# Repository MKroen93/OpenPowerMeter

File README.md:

# OpenPowerMeter
An open source power meter design including hardware and software

This is an open source power meter design. It is compatible with the **YHDC SCT-013-000** current clamp to measure AC mains current without contact. Optionally, 3 phase mains voltage can be measured by connecting it to the bottom screw terminal. The PCB is designed to fit into the Bopla CNC 87.5 DIN rail casing and consists on a lower and upper half of hardware which fit together through 2.54 mm pinheaders.

The lower part contains the analog frontend for converting the input signals to true rms values and for converting the input waveforms to a rectangular 3.3V output signal which can be used to detect the phase using a simple timer.

The upper part contains the MCU (ESP32) and ADC and is not yet finished.

**Please note:** This project is currently in early development and not yet tested or ready to be used.

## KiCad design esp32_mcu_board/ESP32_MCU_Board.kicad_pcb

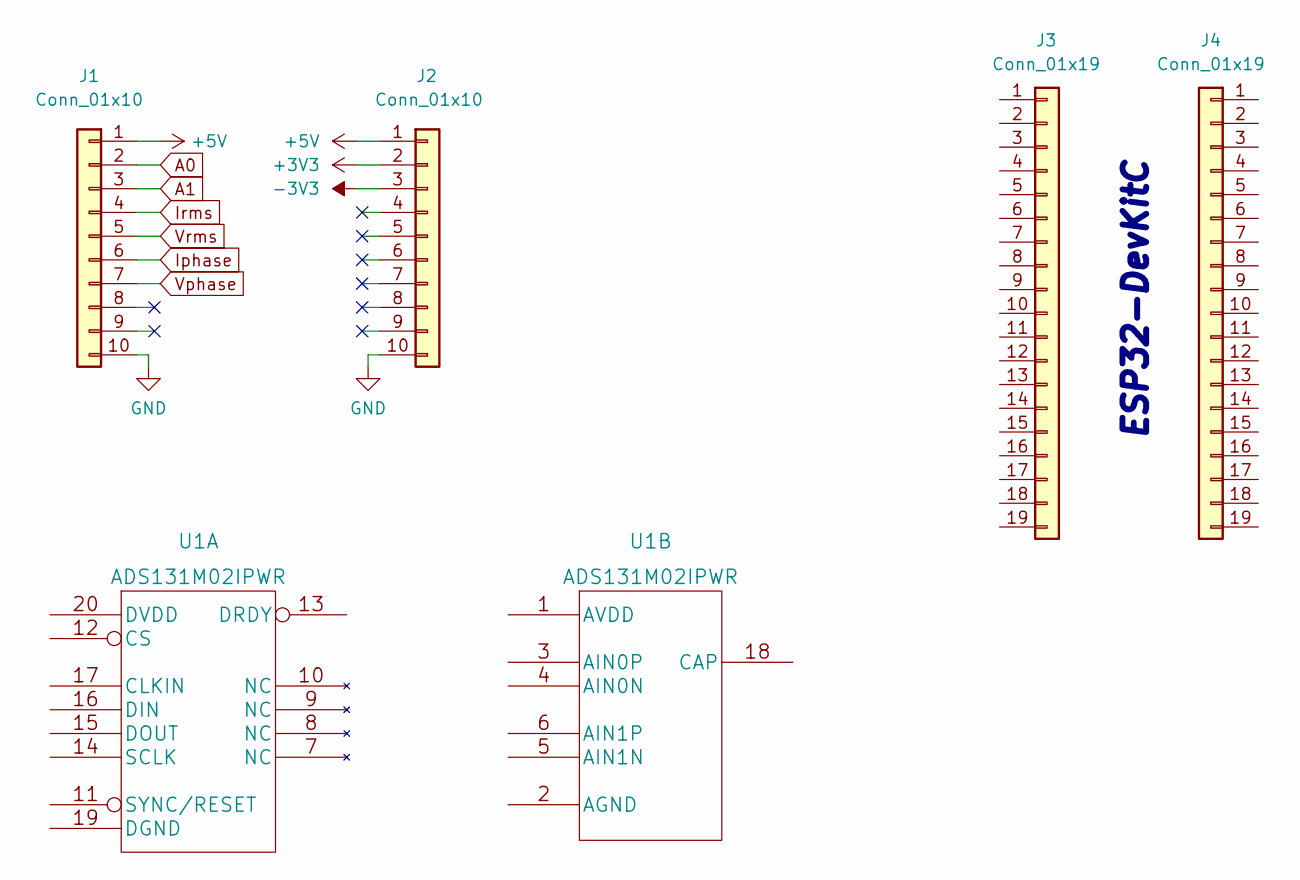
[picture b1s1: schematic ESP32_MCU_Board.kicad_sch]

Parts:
J1, J2: Conn_01x10; PinSocket_1x10_P2.54mm_Vertical
J3, J4: Conn_01x19; PinSocket_1x19_P2.54mm_Vertical
U1: ADS131M02IPWR

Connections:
+3V3: J2.2
+5V: J1.1, J2.1
-3V3: J2.3
A0: J1.2
A1: J1.3
GND: J1.10, J2.10
Iphase: J1.6
Irms: J1.4
Vphase: J1.7
Vrms: J1.5

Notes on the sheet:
ESP32-DevKitC

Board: 2 copper layers, 5 parts (2 on the bottom side), 2 nets, no tracks yet.

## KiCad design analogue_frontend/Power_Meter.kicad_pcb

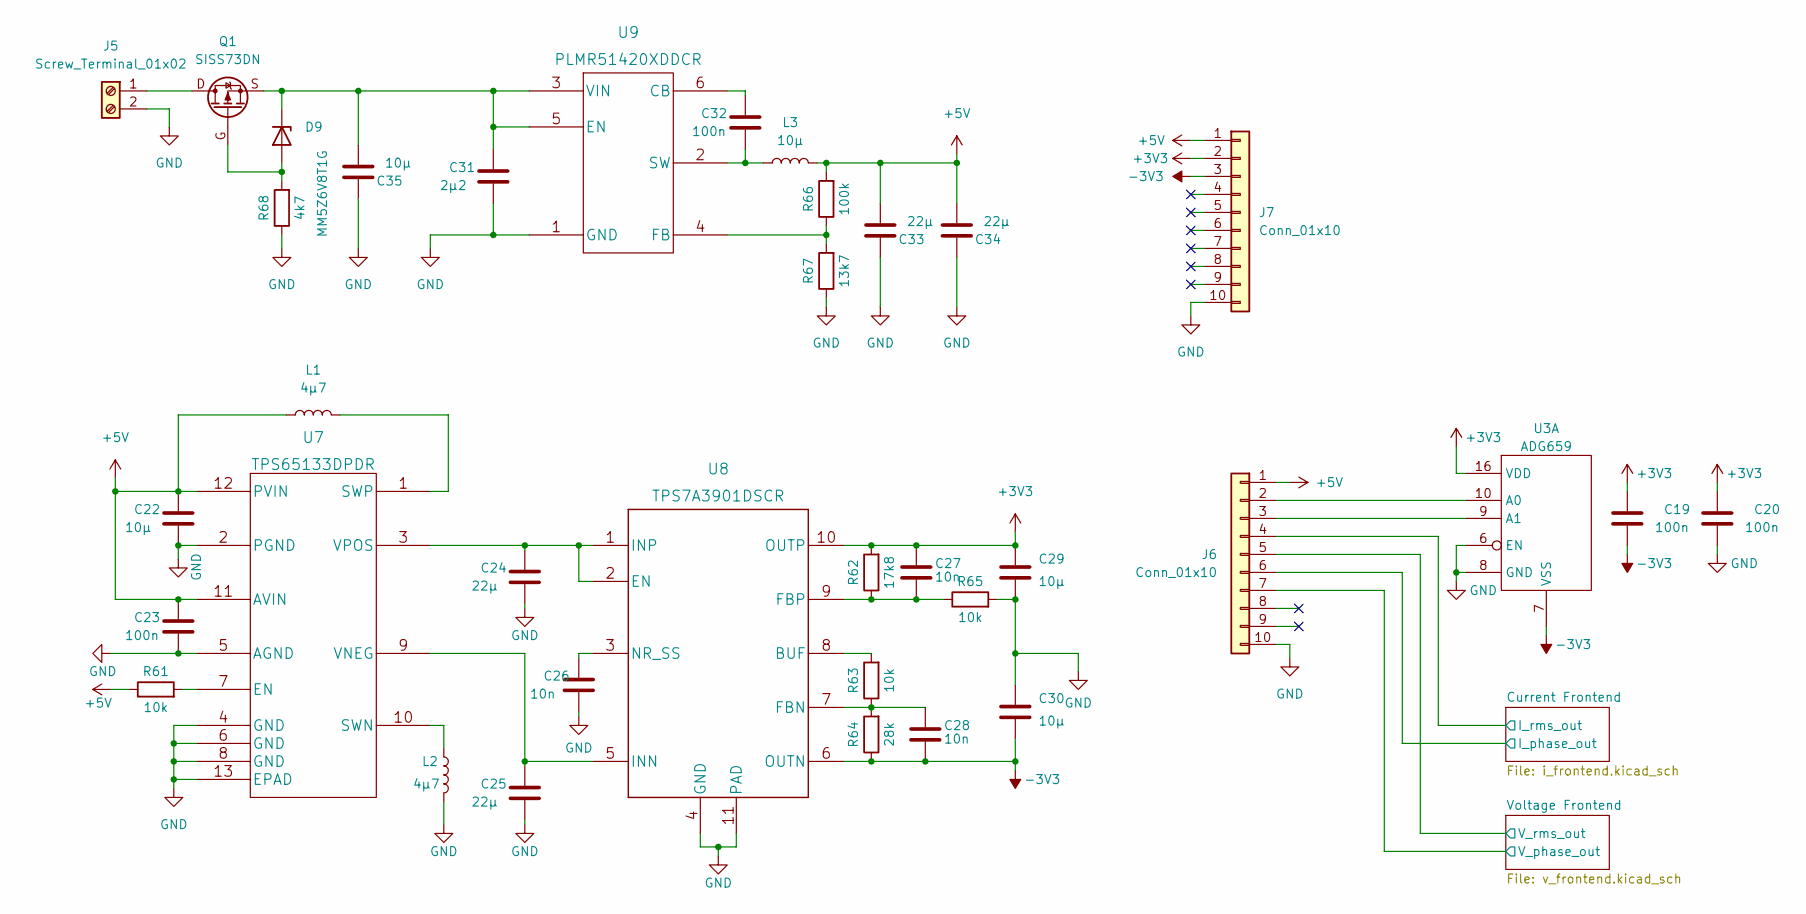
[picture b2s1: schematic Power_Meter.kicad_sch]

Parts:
C19, C23: 100n; C_0603_1608Metric_Pad1.08x0.95mm_HandSolder; Voltage rating 10V
C20: 100n; C_0603_1608Metric_Pad1.08x0.95mm_HandSolder; Voltage rating 6.3V
C22: 10µ; C_0805_2012Metric_Pad1.18x1.45mm_HandSolder; Voltage rating 10V
C24, C25, C33, C34: 22µ; C_0805_2012Metric_Pad1.18x1.45mm_HandSolder; Voltage rating 10V
C26: 10n; C_0603_1608Metric_Pad1.08x0.95mm_HandSolder; Voltage rating 10V
C27, C28: 10n; C_0603_1608Metric_Pad1.08x0.95mm_HandSolder; Voltage rating 6.3V
C29, C30: 10µ; C_0805_2012Metric_Pad1.18x1.45mm_HandSolder; Voltage rating 6.3V
C31: 2µ2; C_0805_2012Metric_Pad1.18x1.45mm_HandSolder; Voltage rating 35V
C32: 100n; C_0603_1608Metric_Pad1.08x0.95mm_HandSolder; Voltage rating 16V
C35: 10µ; C_0805_2012Metric_Pad1.18x1.45mm_HandSolder; Voltage rating 35V
D9: MM5Z6V8T1G; D_SOD-523
J5: Screw_Terminal_01x02; TerminalBlock_Phoenix_MKDS-1,5-2-5.08_1x02_P5.08mm_Horizont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
J6, J7: Conn_01x10; PinHeader_1x10_P2.54mm_Vertical
L1, L2: 4µ7; L_Coilcraft_XxL4020; Part nr. XFL4020-472ME_
L3: 10µ; L_Coilcraft_XxL4020; Part nr. XAL4040-103ME_
Q1: SISS73DN; Vishay_PowerPAK_1212-8_Single
R61, R63, R65: 10k; R_0603_1608Metric_Pad0.98x0.95mm_HandSolder
R62: 17k8; R_0603_1608Metric_Pad0.98x0.95mm_HandSolder
R64: 28k; R_0603_1608Metric_Pad0.98x0.95mm_HandSolder
R66: 100k; R_0603_1608Metric_Pad0.98x0.95mm_HandSolder
R67: 13k7; R_0603_1608Metric_Pad0.98x0.95mm_HandSolder
R68: 4k7; R_0603_1608Metric_Pad0.98x0.95mm_HandSolder
U3: ADG659; ADG659YRUZ
U7: TPS65133DPDR
U8: TPS7A3901DSCR
U9: PLMR51420XDDCR; PLMR51420XDDCT

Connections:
+3V3: C19.1, C20.1, C27.1, C29.1, J7.2, R62.2, U3.16 (VDD), U8.10 (OUTP); also elsewhere on the board
+5V: C22.1, C23.1, C33.2, C34.2, J6.1, J7.1, L1.1, L3.2, R61.1, R66.2, U7.11 (AVIN), U7.12 (PVIN)
-3V3: C19.2, C28.2, C30.2, J7.3, R64.1, U3.7 (VSS), U8.6 (OUTN); also elsewhere on the board
/Current Frontend/I_phase_out: J6.6; also elsewhere on the board
/Current Frontend/I_rms_out: J6.4; also elsewhere on the board
/Voltage Frontend/V_phase_out: J6.7; also elsewhere on the board
/Voltage Frontend/V_rms_out: J6.5; also elsewhere on the board
GND: C20.2, C22.2, C23.2, C24.2, C25.2, C26.2, C29.2, C30.1, C31.2, C33.1, C34.1, C35.1, J5.2, J6.10, J7.10, L2.2, R65.2, R67.1, R68.1, U3.6 (EN), U3.8 (GND), U7.2 (PGND), U7.4 (GND), U7.5 (AGND), U7.6 (GND), U7.8 (GND), U7.13 (EPAD), U8.4 (GND), U8.11 (PAD), U9.1 (GND); also elsewhere on the board
unnamed: C24.1, U7.3 (VPOS), U8.1 (INP), U8.2 (EN)
unnamed: C25.1, U7.9 (VNEG), U8.5 (INN)
unnamed: C26.1, U8.3 (NR_SS)
unnamed: C27.2, R62.1, R65.1, U8.9 (FBP)
unnamed: C28.1, R63.1, R64.2, U8.7 (FBN)
unnamed: C31.1, C35.2, D9.1 (K), Q1.S, U9.3 (VIN), U9.5 (EN)
unnamed: C32.1, U9.6 (CB)
unnamed: C32.2, L3.1, U9.2 (SW)
unnamed: D9.2 (A), Q1.G, R68.2
unnamed: J5.1, Q1.D
unnamed: J6.2, U3.10 (A0)
unnamed: J6.3, U3.9 (A1)
unnamed: L1.2, U7.1 (SWP)
unnamed: L2.1, U7.10 (SWN)
unnamed: R61.2, U7.7 (EN)
unnamed: R63.2, U8.8 (BUF)
unnamed: R66.1, R67.2, U9.4 (FB)

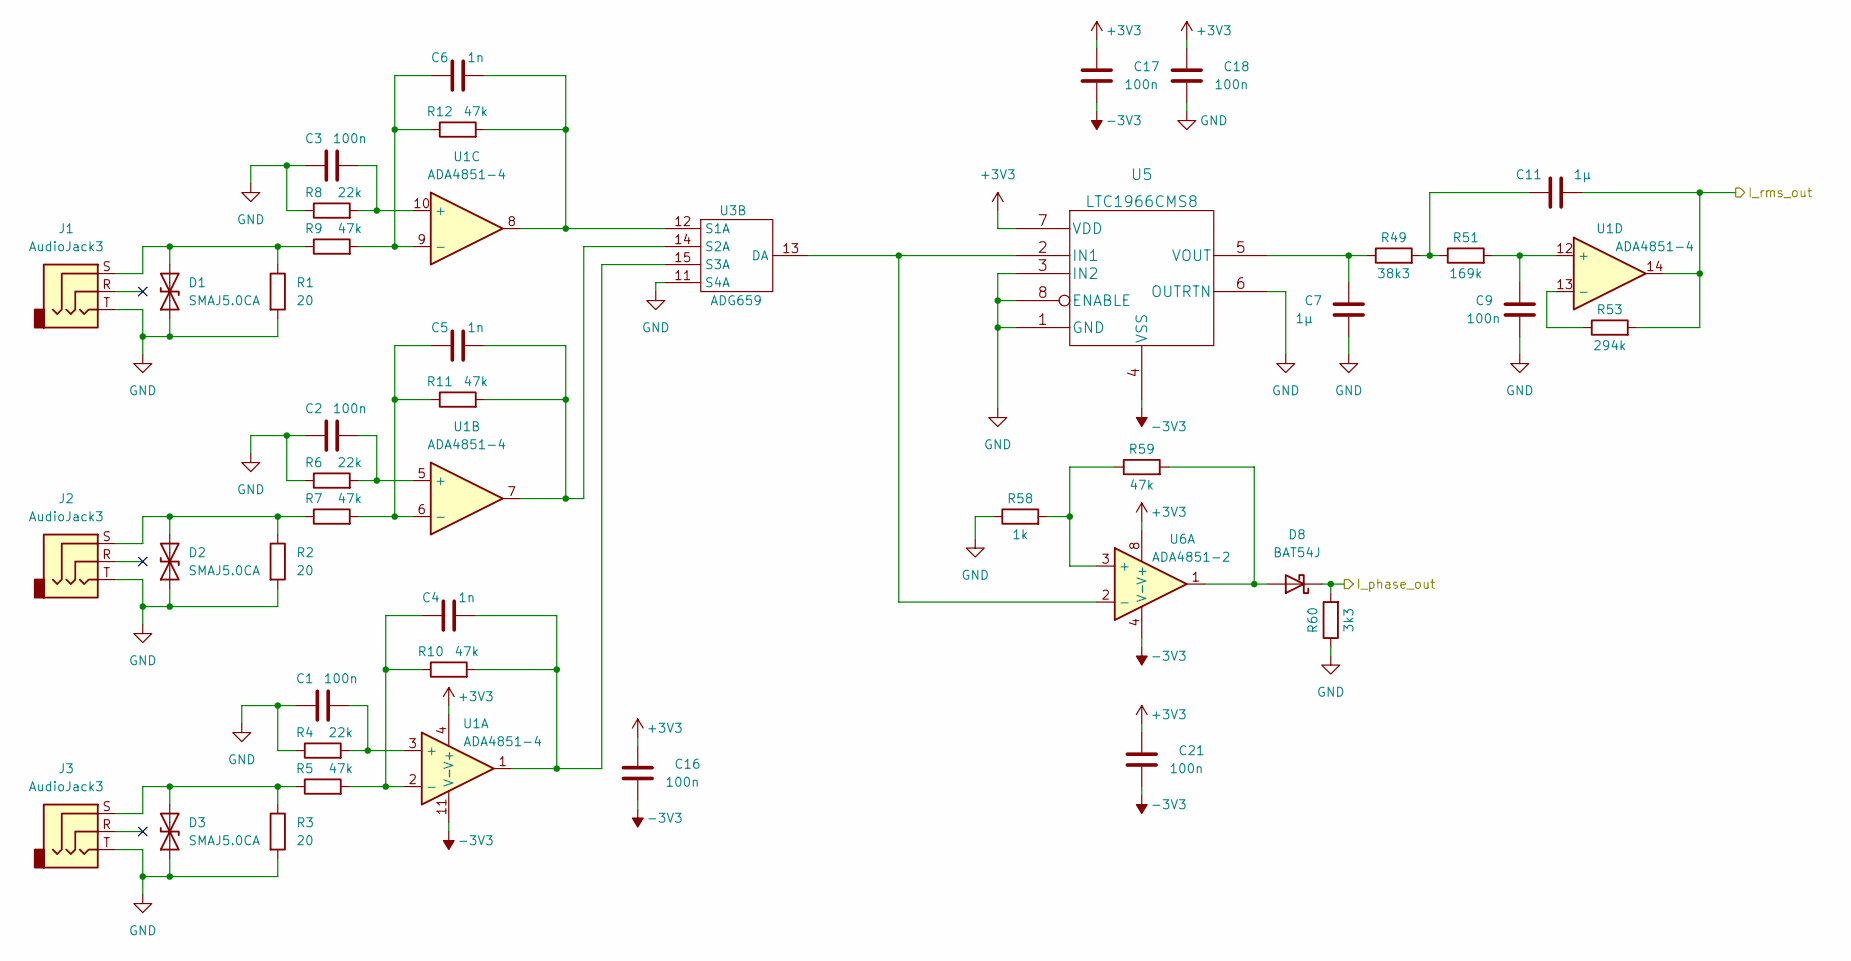
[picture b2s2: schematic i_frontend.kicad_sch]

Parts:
C1, C2, C3, C9, C18: 100n; C_0603_1608Metric_Pad1.08x0.95mm_HandSolder; Voltage rating 6.3V
C4, C5, C6: 1n; C_0603_1608Metric_Pad1.08x0.95mm_HandSolder; Voltage rating 6.3V
C7, C11: 1µ; C_0603_1608Metric_Pad1.08x0.95mm_HandSolder; Voltage rating 6.3V
C16, C17, C21: 100n; C_0603_1608Metric_Pad1.08x0.95mm_HandSolder; Voltage rating 10V
D1, D2, D3: SMAJ5.0CA; D_SMA_Handsoldering
D8: BAT54J; D_SOD-323F
J1, J2, J3: AudioJack3; Jack_3.5mm_CUI_SJ-3523-SMT_Horizontal
R1, R2, R3: 20; R_1206_3216Metric_Pad1.30x1.75mm_HandSolder
R4, R6, R8: 22k; R_0603_1608Metric_Pad0.98x0.95mm_HandSolder
R5, R7, R9, R10, R11, R12, R59: 47k; R_0603_1608Metric_Pad0.98x0.95mm_HandSolder
R49: 38k3; R_0603_1608Metric_Pad0.98x0.95mm_HandSolder
R51: 169k; R_0603_1608Metric_Pad0.98x0.95mm_HandSolder
R53: 294k; R_0603_1608Metric_Pad0.98x0.95mm_HandSolder
R58: 1k; R_0603_1608Metric_Pad0.98x0.95mm_HandSolder
R60: 3k3; R_0603_1608Metric_Pad0.98x0.95mm_HandSolder
U1: ADA4851-4; ADA4851-4YRUZ
U3: ADG659; ADG659YRUZ
U5: LTC1966CMS8
U6: ADA4851-2; ADA4851-2YRMZ

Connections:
+3V3: C16.1, C17.1, C18.1, C21.1, U1.4 (V+), U5.7 (VDD), U6.8 (V+); also elsewhere on the board
-3V3: C16.2, C17.2, C21.2, U1.11 (V-), U5.4 (VSS), U6.4 (V-); also elsewhere on the board
/Current Frontend/I_phase_out: D8.1 (K), R60.2; also elsewhere on the board
/Current Frontend/I_rms_out: C11.2, R53.2, U1.14; also elsewhere on the board
GND: C1.1, C2.1, C3.1, C7.2, C9.2, C18.2, D1.1 (A1), D2.1 (A1), D3.1 (A1), J1.T, J2.T, J3.T, R1.2, R2.2, R3.2, R4.1, R6.1, R8.1, R58.1, R60.1, U3.11 (S4A), U5.1 (GND), U5.3 (IN2), U5.6 (OUTRTN), U5.8 (ENABLE); also elsewhere on the board
unnamed: C1.2, R4.2, U1.3 (+)
unnamed: C2.2, R6.2, U1.5 (+)
unnamed: C3.2, R8.2, U1.10 (+)
unnamed: C4.1, R5.2, R10.1, U1.2 (-)
unnamed: C4.2, R10.2, U1.1, U3.15 (S3A)
unnamed: C5.1, R7.2, R11.1, U1.6 (-)
unnamed: C5.2, R11.2, U1.7, U3.14 (S2A)
unnamed: C6.1, R9.2, R12.1, U1.9 (-)
unnamed: C6.2, R12.2, U1.8, U3.12 (S1A)
unnamed: C7.1, R49.1, U5.5 (VOUT)
unnamed: C9.1, R51.2, U1.12 (+)
unnamed: C11.1, R49.2, R51.1
unnamed: D1.2 (A2), J1.S, R1.1, R9.1
unnamed: D2.2 (A2), J2.S, R2.1, R7.1
unnamed: D3.2 (A2), J3.S, R3.1, R5.1
unnamed: D8.2 (A), R59.2, U6.1
unnamed: R53.1, U1.13 (-)
unnamed: R58.2, R59.1, U6.3 (+)
unnamed: U3.13 (DA), U5.2 (IN1), U6.2 (-)

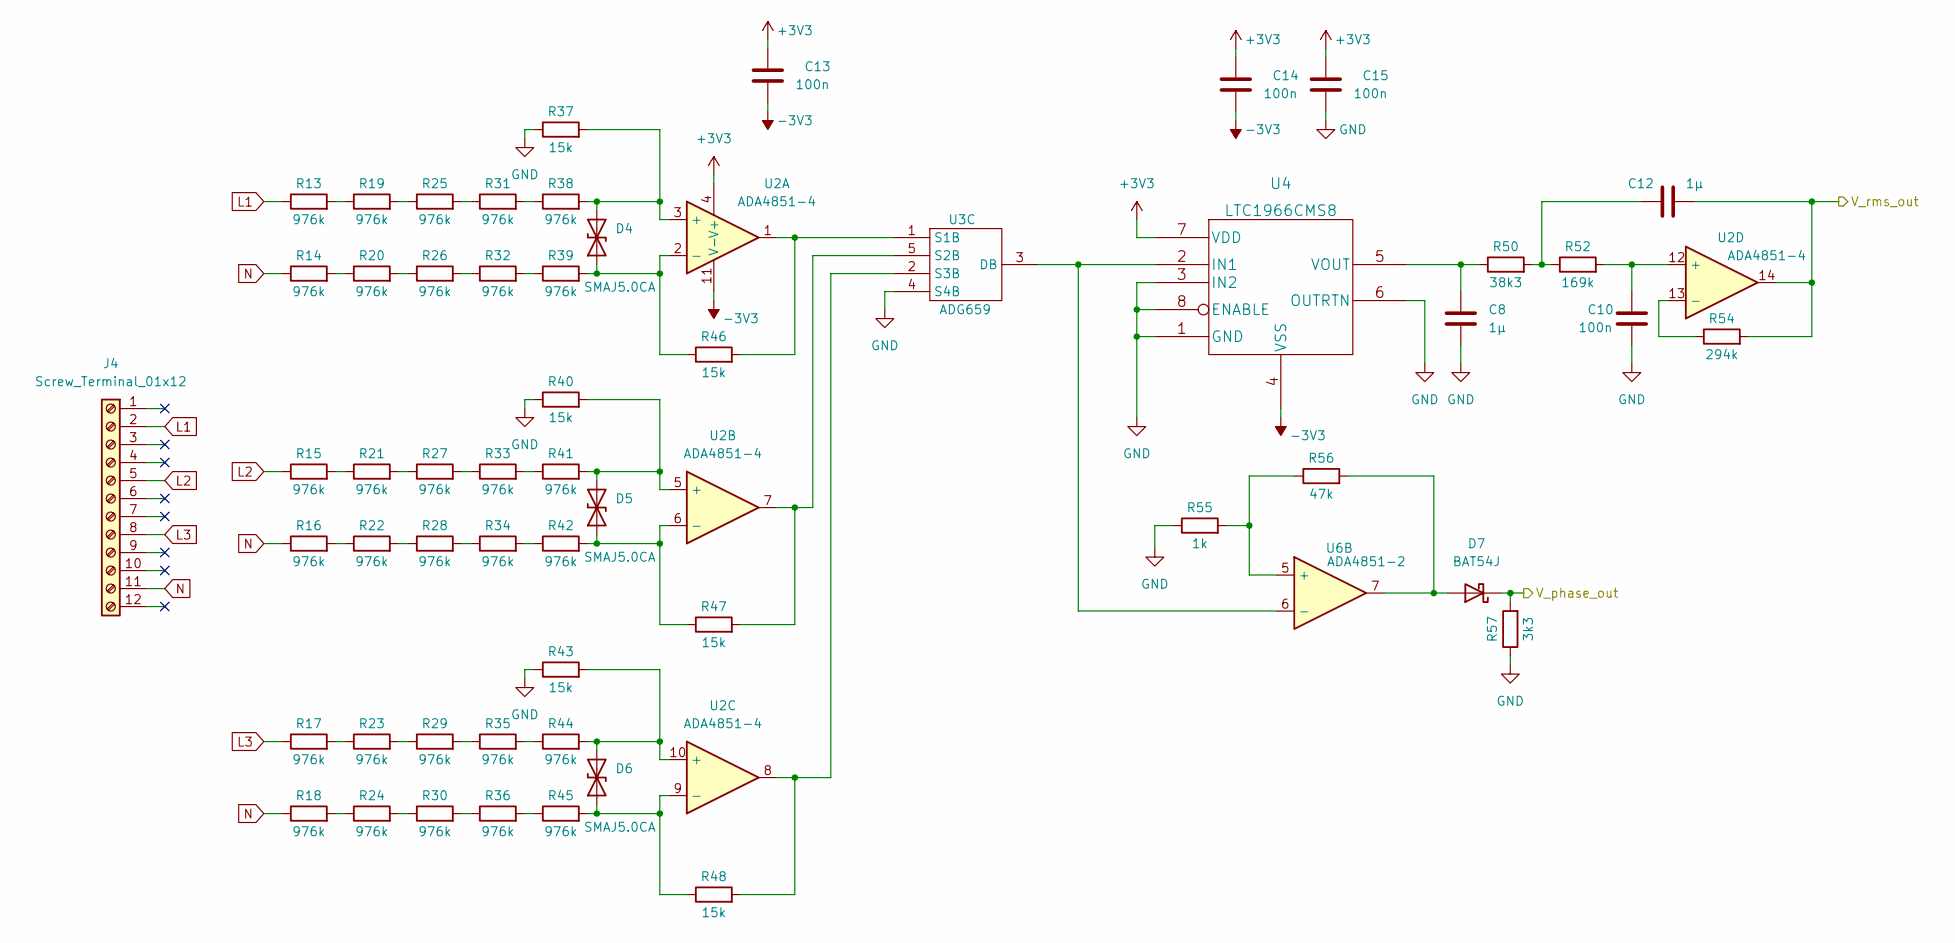
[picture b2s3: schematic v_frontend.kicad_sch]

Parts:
C8, C12: 1µ; C_0603_1608Metric_Pad1.08x0.95mm_HandSolder; Voltage rating 6.3V
C10, C15: 100n; C_0603_1608Metric_Pad1.08x0.95mm_HandSolder; Voltage rating 6.3V
C13, C14: 100n; C_0603_1608Metric_Pad1.08x0.95mm_HandSolder; Voltage rating 10V
D4, D5, D6: SMAJ5.0CA; D_SMA_Handsoldering
D7: BAT54J; D_SOD-323F
J4: Screw_Terminal_01x12; TerminalBlock_Phoenix_MKDS-1,5-12-5.08_1x12_P5.08mm_Horizon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
R13, R14, R15, R16, R17, R18, R19, R20, R21, R22, R23, R24, R25, R26, R27, R28, R29, R30, R31, R32, R33, R34, R35, R36, R38, R39, R41, R42, R44, R45: 976k; R_1210_3225Metric_Pad1.30x2.65mm_HandSolder
R37, R40, R43, R46, R47, R48: 15k; R_0603_1608Metric_Pad0.98x0.95mm_HandSolder
R50: 38k3; R_0603_1608Metric_Pad0.98x0.95mm_HandSolder
R52: 169k; R_0603_1608Metric_Pad0.98x0.95mm_HandSolder
R54: 294k; R_0603_1608Metric_Pad0.98x0.95mm_HandSolder
R55: 1k; R_0603_1608Metric_Pad0.98x0.95mm_HandSolder
R56: 47k; R_0603_1608Metric_Pad0.98x0.95mm_HandSolder
R57: 3k3; R_0603_1608Metric_Pad0.98x0.95mm_HandSolder
U2: ADA4851-4; ADA4851-4YRUZ
U3: ADG659; ADG659YRUZ
U4: LTC1966CMS8
U6: ADA4851-2; ADA4851-2YRMZ

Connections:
+3V3: C13.1, C14.1, C15.1, U2.4 (V+), U4.7 (VDD); also elsewhere on the board
-3V3: C13.2, C14.2, U2.11 (V-), U4.4 (VSS); also elsewhere on the board
/Voltage Frontend/V_phase_out: D7.1 (K), R57.2; also elsewhere on the board
/Voltage Frontend/V_rms_out: C12.2, R54.2, U2.14; also elsewhere on the board
GND: C8.2, C10.2, C15.2, R37.1, R40.1, R43.1, R55.1, R57.1, U3.4 (S4B), U4.1 (GND), U4.3 (IN2), U4.6 (OUTRTN), U4.8 (ENABLE); also elsewhere on the board
L1: J4.2, R13.1
L2: J4.5, R15.1
L3: J4.8, R17.1
N: J4.11, R14.1, R16.1, R18.1
unnamed: C8.1, R50.1, U4.5 (VOUT)
unnamed: C10.1, R52.2, U2.12 (+)
unnamed: C12.1, R50.2, R52.1
unnamed: D4.1 (A1), R39.2, R46.1, U2.2 (-)
unnamed: D4.2 (A2), R37.2, R38.2, U2.3 (+)
unnamed: D5.1 (A1), R42.2, R47.1, U2.6 (-)
unnamed: D5.2 (A2), R40.2, R41.2, U2.5 (+)
unnamed: D6.1 (A1), R45.2, R48.1, U2.9 (-)
unnamed: D6.2 (A2), R43.2, R44.2, U2.10 (+)
unnamed: D7.2 (A), R56.2, U6.7
unnamed: R13.2, R19.1
unnamed: R14.2, R20.1
unnamed: R15.2, R21.1
unnamed: R16.2, R22.1
unnamed: R17.2, R23.1
unnamed: R18.2, R24.1
unnamed: R19.2, R25.1
unnamed: R20.2, R26.1
unnamed: R21.2, R27.1
unnamed: R22.2, R28.1
unnamed: R23.2, R29.1
unnamed: R24.2, R30.1
unnamed: R25.2, R31.1
unnamed: R26.2, R32.1
unnamed: R27.2, R33.1
unnamed: R28.2, R34.1
unnamed: R29.2, R35.1
unnamed: R30.2, R36.1
unnamed: R31.2, R38.1
unnamed: R32.2, R39.1
unnamed: R33.2, R41.1
unnamed: R34.2, R42.1
unnamed: R35.2, R44.1
unnamed: R36.2, R45.1
unnamed: R46.2, U2.1, U3.1 (S1B)
unnamed: R47.2, U2.7, U3.5 (S2B)
unnamed: R48.2, U2.8, U3.2 (S3B)
unnamed: R54.1, U2.13 (-)
unnamed: R55.2, R56.1, U6.5 (+)
unnamed: U3.3 (DB), U4.2 (IN1), U6.6 (-)

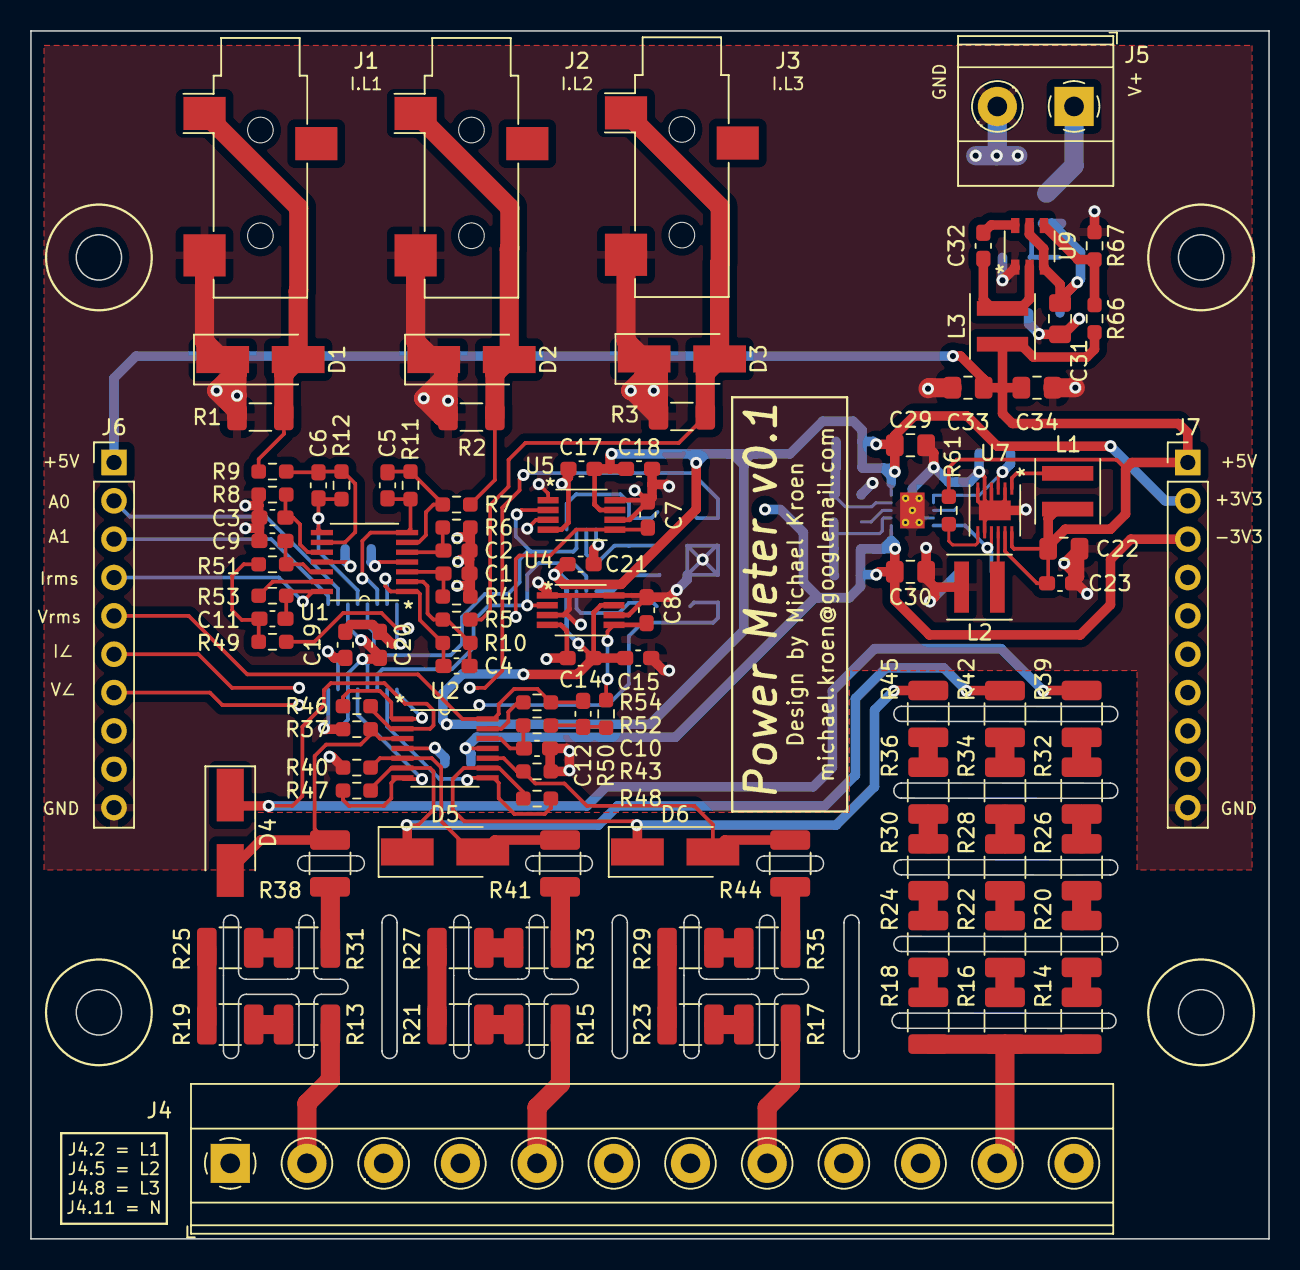
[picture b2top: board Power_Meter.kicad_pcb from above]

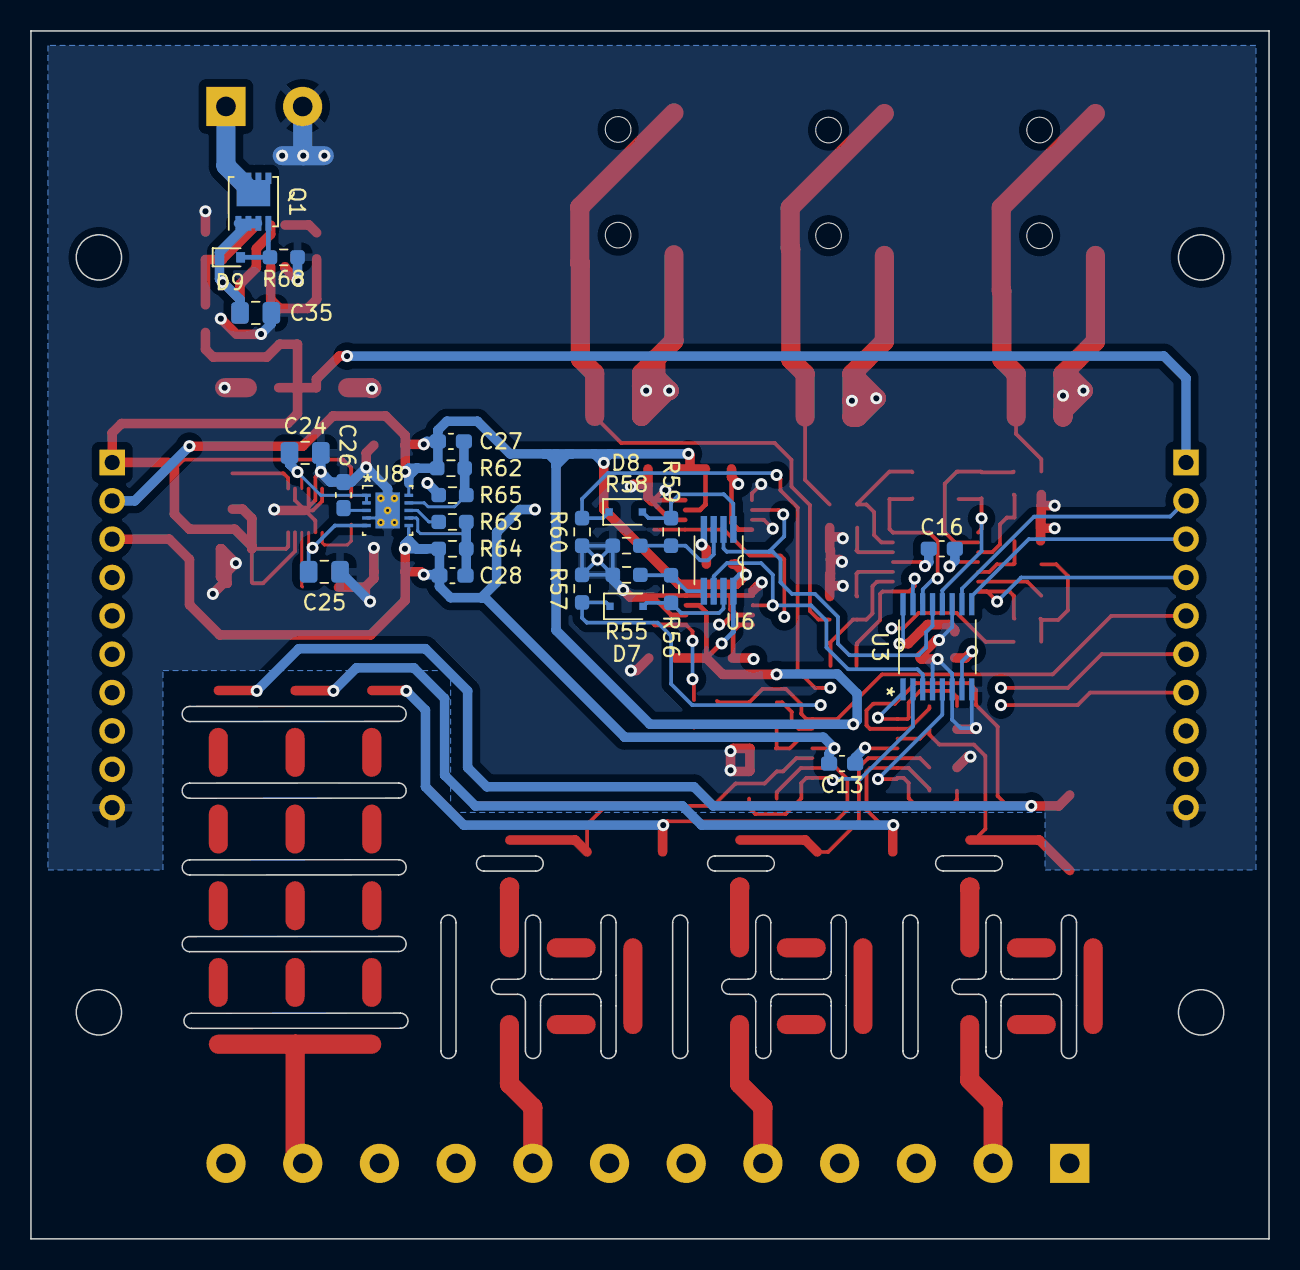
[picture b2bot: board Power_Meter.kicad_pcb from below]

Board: 4 copper layers, 82.0 x 80.0 mm, 132 parts (26 on the bottom side), 88 nets.

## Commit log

2022-11-06 Adding initial hardware design revision
2022-11-06 Adding .pdf exports
2022-11-06 Update README.md
    Added initial project description
2022-11-06 Changing folder structure to destinguish analogue / digital part
2022-11-06 Added ESP32 MCU board design (WiP)
2022-11-06 Added ESP32 MCU board to project description
2022-11-06 Added ADS131M02IPWR ADC for MCU board to symbol and footprint library

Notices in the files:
parts and their libraries:
Copyright 2021 Accelerated Designs. All rights reserved.
